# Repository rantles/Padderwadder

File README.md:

# Padderwadder
Padderwadder is a simple 3-key macropad featuring an OLED Display and a rotary encoder! I programmed this macropad for the game osu! using QMK Firmware. This is my first ever hardware project, so I got to learn how to use a ton of new programs throughout the process :D

## Features
- 3 keys
- A 0.91 inch OLED Display
- EC11 Rotary encoder
- A 3D printed case
- QMK Firmware

## CAD
Heres my CAD model, made in Fusion 360! The case is held together by 4 M3 Bolts and heatset inserts. I think I spent almost half of my time researching and figuring things out but I had fun :)

| Top                            | Middle                              | Middle                               |
| ------------------------------ | ----------------------------------- | ------------------------------------ |
|  |  |  |

## PCB
My PCB, made in KiCad 10.0

**Schematic**:

**PCB**:

## Firmware Overview
This entire macropad uses QMK Firmware.

The rotary encoder is programmed to rotate to change volume, and press to mute.

## BOM
Everything needed for this design:
- 1 unsoldered Seeed XIAO RP2040
- 3x MX-Style switches
- 4x White blank DSA Keycaps
- 1x 0.91 inch 128x32 OLED display
- 1x EC11 Rotary Encoder
- 4x M3x16mm screws
- 4x M3x5mx4mm heatset inserts
- 3D printed case

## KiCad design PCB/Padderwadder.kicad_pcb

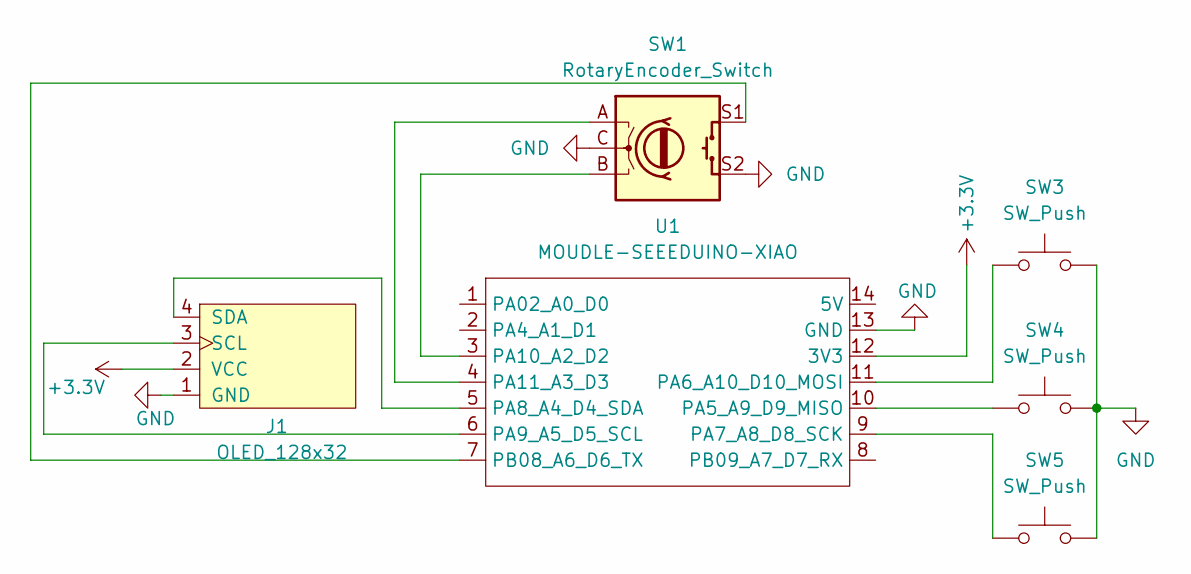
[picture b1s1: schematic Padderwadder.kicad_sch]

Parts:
J1: OLED_128x32
SW1: RotaryEncoder_Switch; RotaryEncoder_Alps_EC11E-Switch_Vertical_H20mm
SW3, SW4, SW5: SW_Push; SW_Cherry_MX_1.00u_PCB
U1: MOUDLE-SEEEDUINO-XIAO; XIAO-Generic-Hybrid-14P-2.54-21X17.8MM

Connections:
+3.3V: J1.2 (VCC), U1.12 (3V3)
GND: J1.1 (GND), SW1.C, SW1.S2, SW3.2, SW4.2, SW5.2, U1.13 (GND)
unnamed: J1.3 (SCL), U1.6 (PA9_A5_D5_SCL)
unnamed: J1.4 (SDA), U1.5 (PA8_A4_D4_SDA)
unnamed: SW4.1, U1.10 (PA5_A9_D9_MISO)
unnamed: SW3.1, U1.11 (PA6_A10_D10_MOSI)
unnamed: SW5.1, U1.9 (PA7_A8_D8_SCK)
unnamed: SW1.B, U1.3 (PA10_A2_D2)
unnamed: SW1.A, U1.4 (PA11_A3_D3)
unnamed: SW1.S1, U1.7 (PB08_A6_D6_TX)

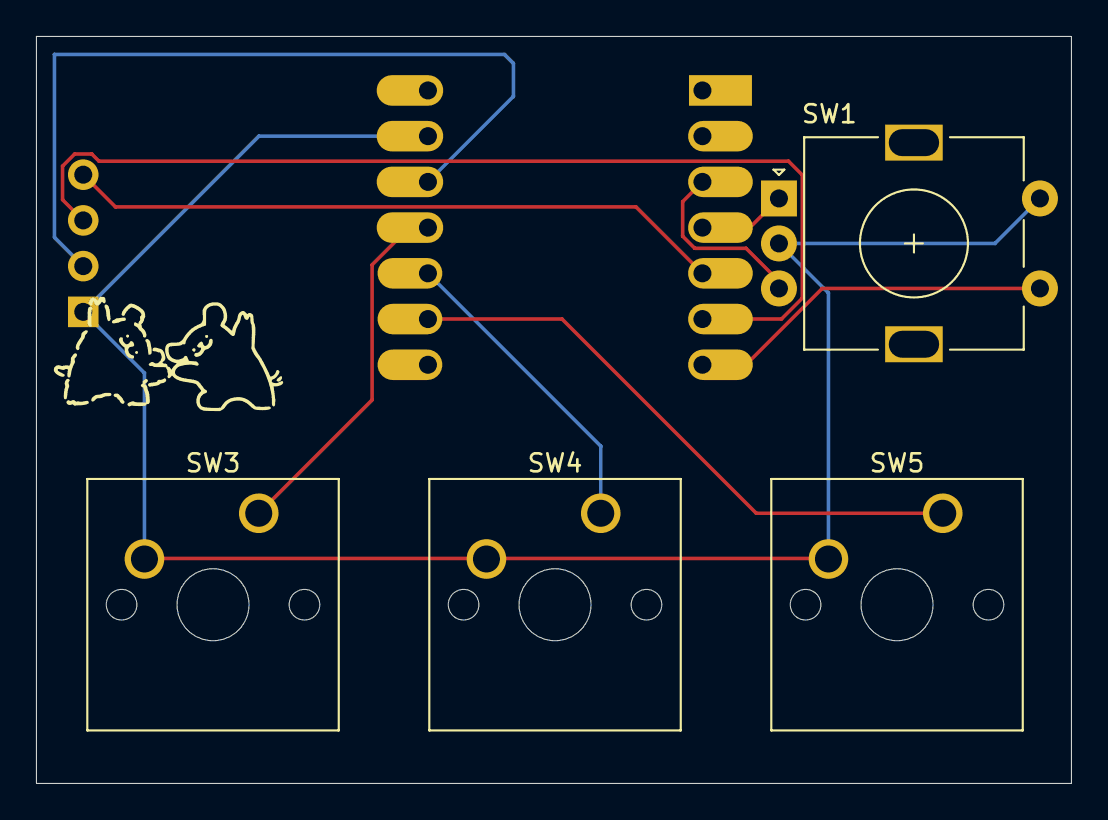
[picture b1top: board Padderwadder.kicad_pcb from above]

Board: 2 copper layers, 57.5 x 41.5 mm, 6 parts (1 on the bottom side), 10 nets.
